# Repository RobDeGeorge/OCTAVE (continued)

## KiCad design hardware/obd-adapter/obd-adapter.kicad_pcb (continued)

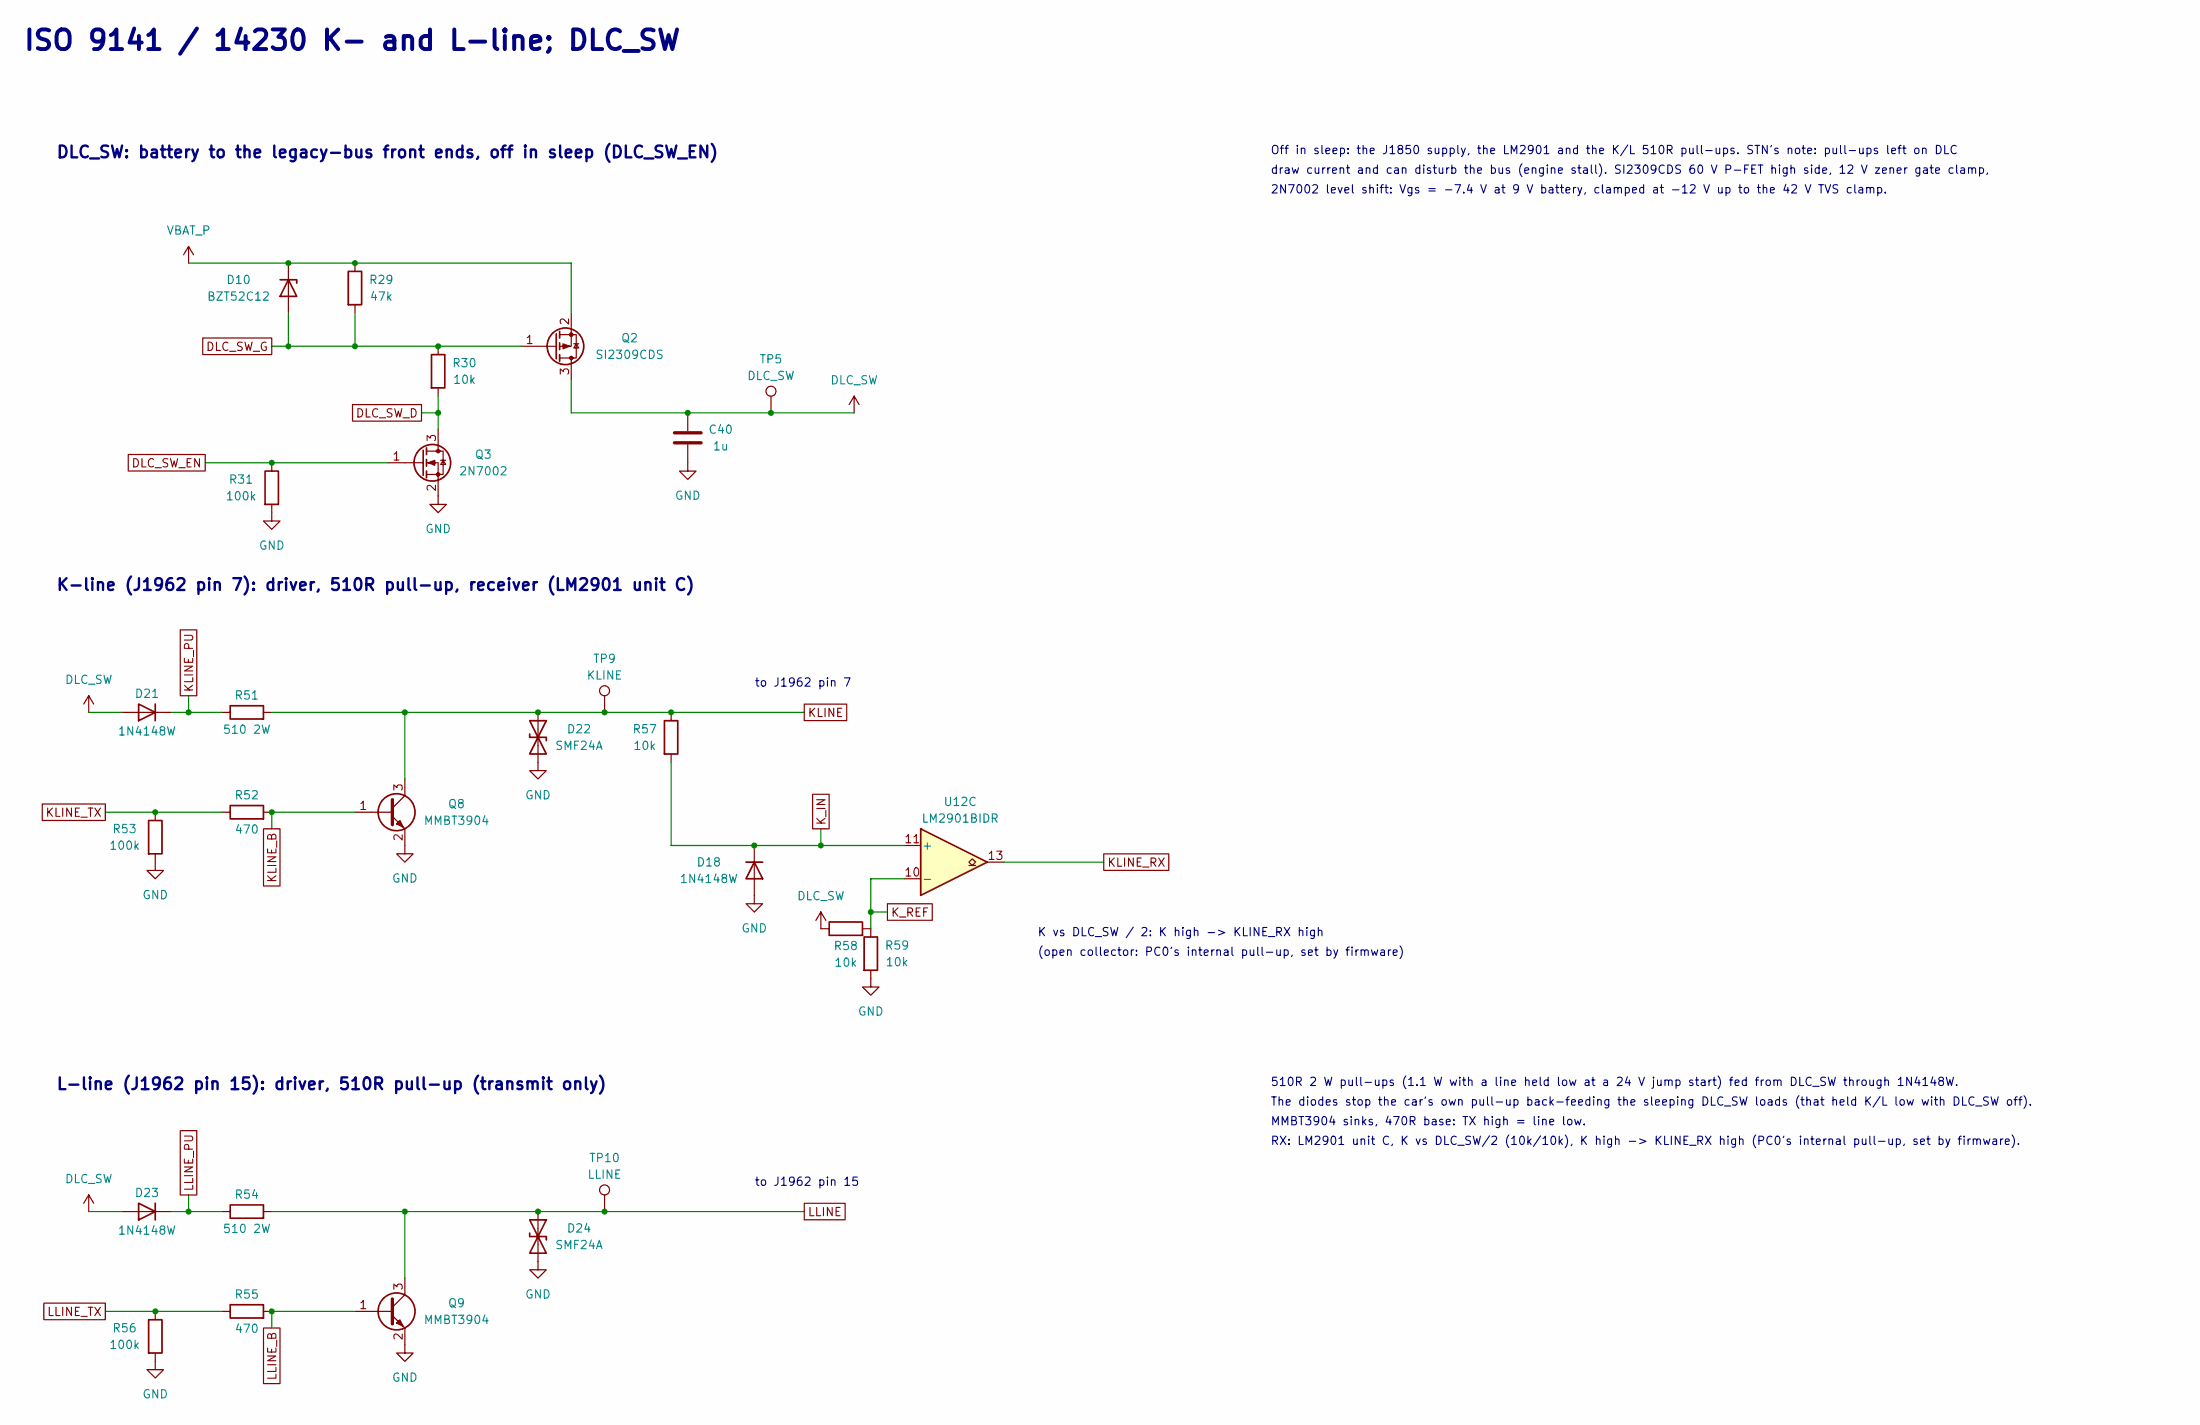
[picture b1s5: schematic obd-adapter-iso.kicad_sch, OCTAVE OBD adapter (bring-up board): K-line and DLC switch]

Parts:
C40: 1u; C_0603_1608Metric; LCSC C15849
D10: BZT52C12; D_SOD-123; LCSC C19077410
D18, D21, D23: 1N4148W; D_SOD-123; LCSC C81598
D22, D24: SMF24A; D_SOD-123F; LCSC C19077514
Q2: SI2309CDS; SOT-23; LCSC C10493
Q3: 2N7002; SOT-23; LCSC C8545
Q8, Q9: MMBT3904; SOT-23; LCSC C20526
R29: 47k; R_0603_1608Metric; LCSC C25819
R30: 10k; R_1206_3216Metric; LCSC C17902
R31, R53, R56: 100k; R_0603_1608Metric; LCSC C25803
R51, R54: 510 2W; R_2512_6332Metric; LCSC C5843118
R52, R55: 470; R_0603_1608Metric; LCSC C23179
R57, R58, R59: 10k; R_0603_1608Metric; LCSC C25804
TP5: DLC_SW; TestPoint_Pad_D1.5mm
TP9: KLINE; TestPoint_Pad_D1.5mm
TP10: LLINE; TestPoint_Pad_D1.5mm
U12: LM2901BIDR; SOIC-14_3.9x8.7mm_P1.27mm; LCSC C22427890

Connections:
DLC_SW: C40.1, D21.2 (A), D23.2 (A), Q2.3 (D), R58.1, TP5.1; also elsewhere on the board
DLC_SW_D: Q3.3 (D), R30.2
DLC_SW_EN: Q3.1 (G), R31.1; also elsewhere on the board
DLC_SW_G: D10.2 (A), Q2.1 (G), R29.2, R30.1
GND: C40.2, D18.2 (A), D22.2 (A2), D24.2 (A2), Q3.2 (S), Q8.2 (E), Q9.2 (E), R31.2, R53.2, R56.2, R59.2; also elsewhere on the board
KLINE: D22.1 (A1), Q8.3 (C), R51.2, R57.1, TP9.1; also elsewhere on the board
KLINE_B: Q8.1 (B), R52.2
KLINE_PU: D21.1 (K), R51.1
KLINE_RX: U12.13; also elsewhere on the board
KLINE_TX: R52.1, R53.1; also elsewhere on the board
K_IN: D18.1 (K), R57.2, U12.11 (+)
K_REF: R58.2, R59.1, U12.10 (-)
LLINE: D24.1 (A1), Q9.3 (C), R54.2, TP10.1; also elsewhere on the board
LLINE_B: Q9.1 (B), R55.2
LLINE_PU: D23.1 (K), R54.1
LLINE_TX: R55.1, R56.1; also elsewhere on the board
VBAT_P: D10.1 (K), Q2.2 (S), R29.1; also elsewhere on the board

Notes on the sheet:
ISO 9141 / 14230 K- and L-line; DLC_SW
DLC_SW: battery to the legacy-bus front ends, off in sleep (DLC_SW_EN)
K-line (J1962 pin 7): driver, 510R pull-up, receiver (LM2901 unit C)
to J1962 pin 7
K vs DLC_SW / 2: K high -> KLINE_RX high
(open collector: PC0's internal pull-up, set by firmware)
L-line (J1962 pin 15): driver, 510R pull-up (transmit only)
to J1962 pin 15
510R 2 W pull-ups (1.1 W with a line held low at a 24 V jump start) fed from DLC_SW through 1N4148W.
The diodes stop the car's own pull-up back-feeding the sleeping DLC_SW loads (that held K/L low with DLC_SW off).
MMBT3904 sinks, 470R base: TX high = line low.
RX: LM2901 unit C, K vs DLC_SW/2 (10k/10k), K high -> KLINE_RX high (PC0's internal pull-up, set by firmware).
Off in sleep: the J1850 supply, the LM2901 and the K/L 510R pull-ups. STN's note: pull-ups left on DLC
draw current and can disturb the bus (engine stall). SI2309CDS 60 V P-FET high side, 12 V zener gate clamp,
2N7002 level shift: Vgs = -7.4 V at 9 V battery, clamped at -12 V up to the 42 V TVS clamp.

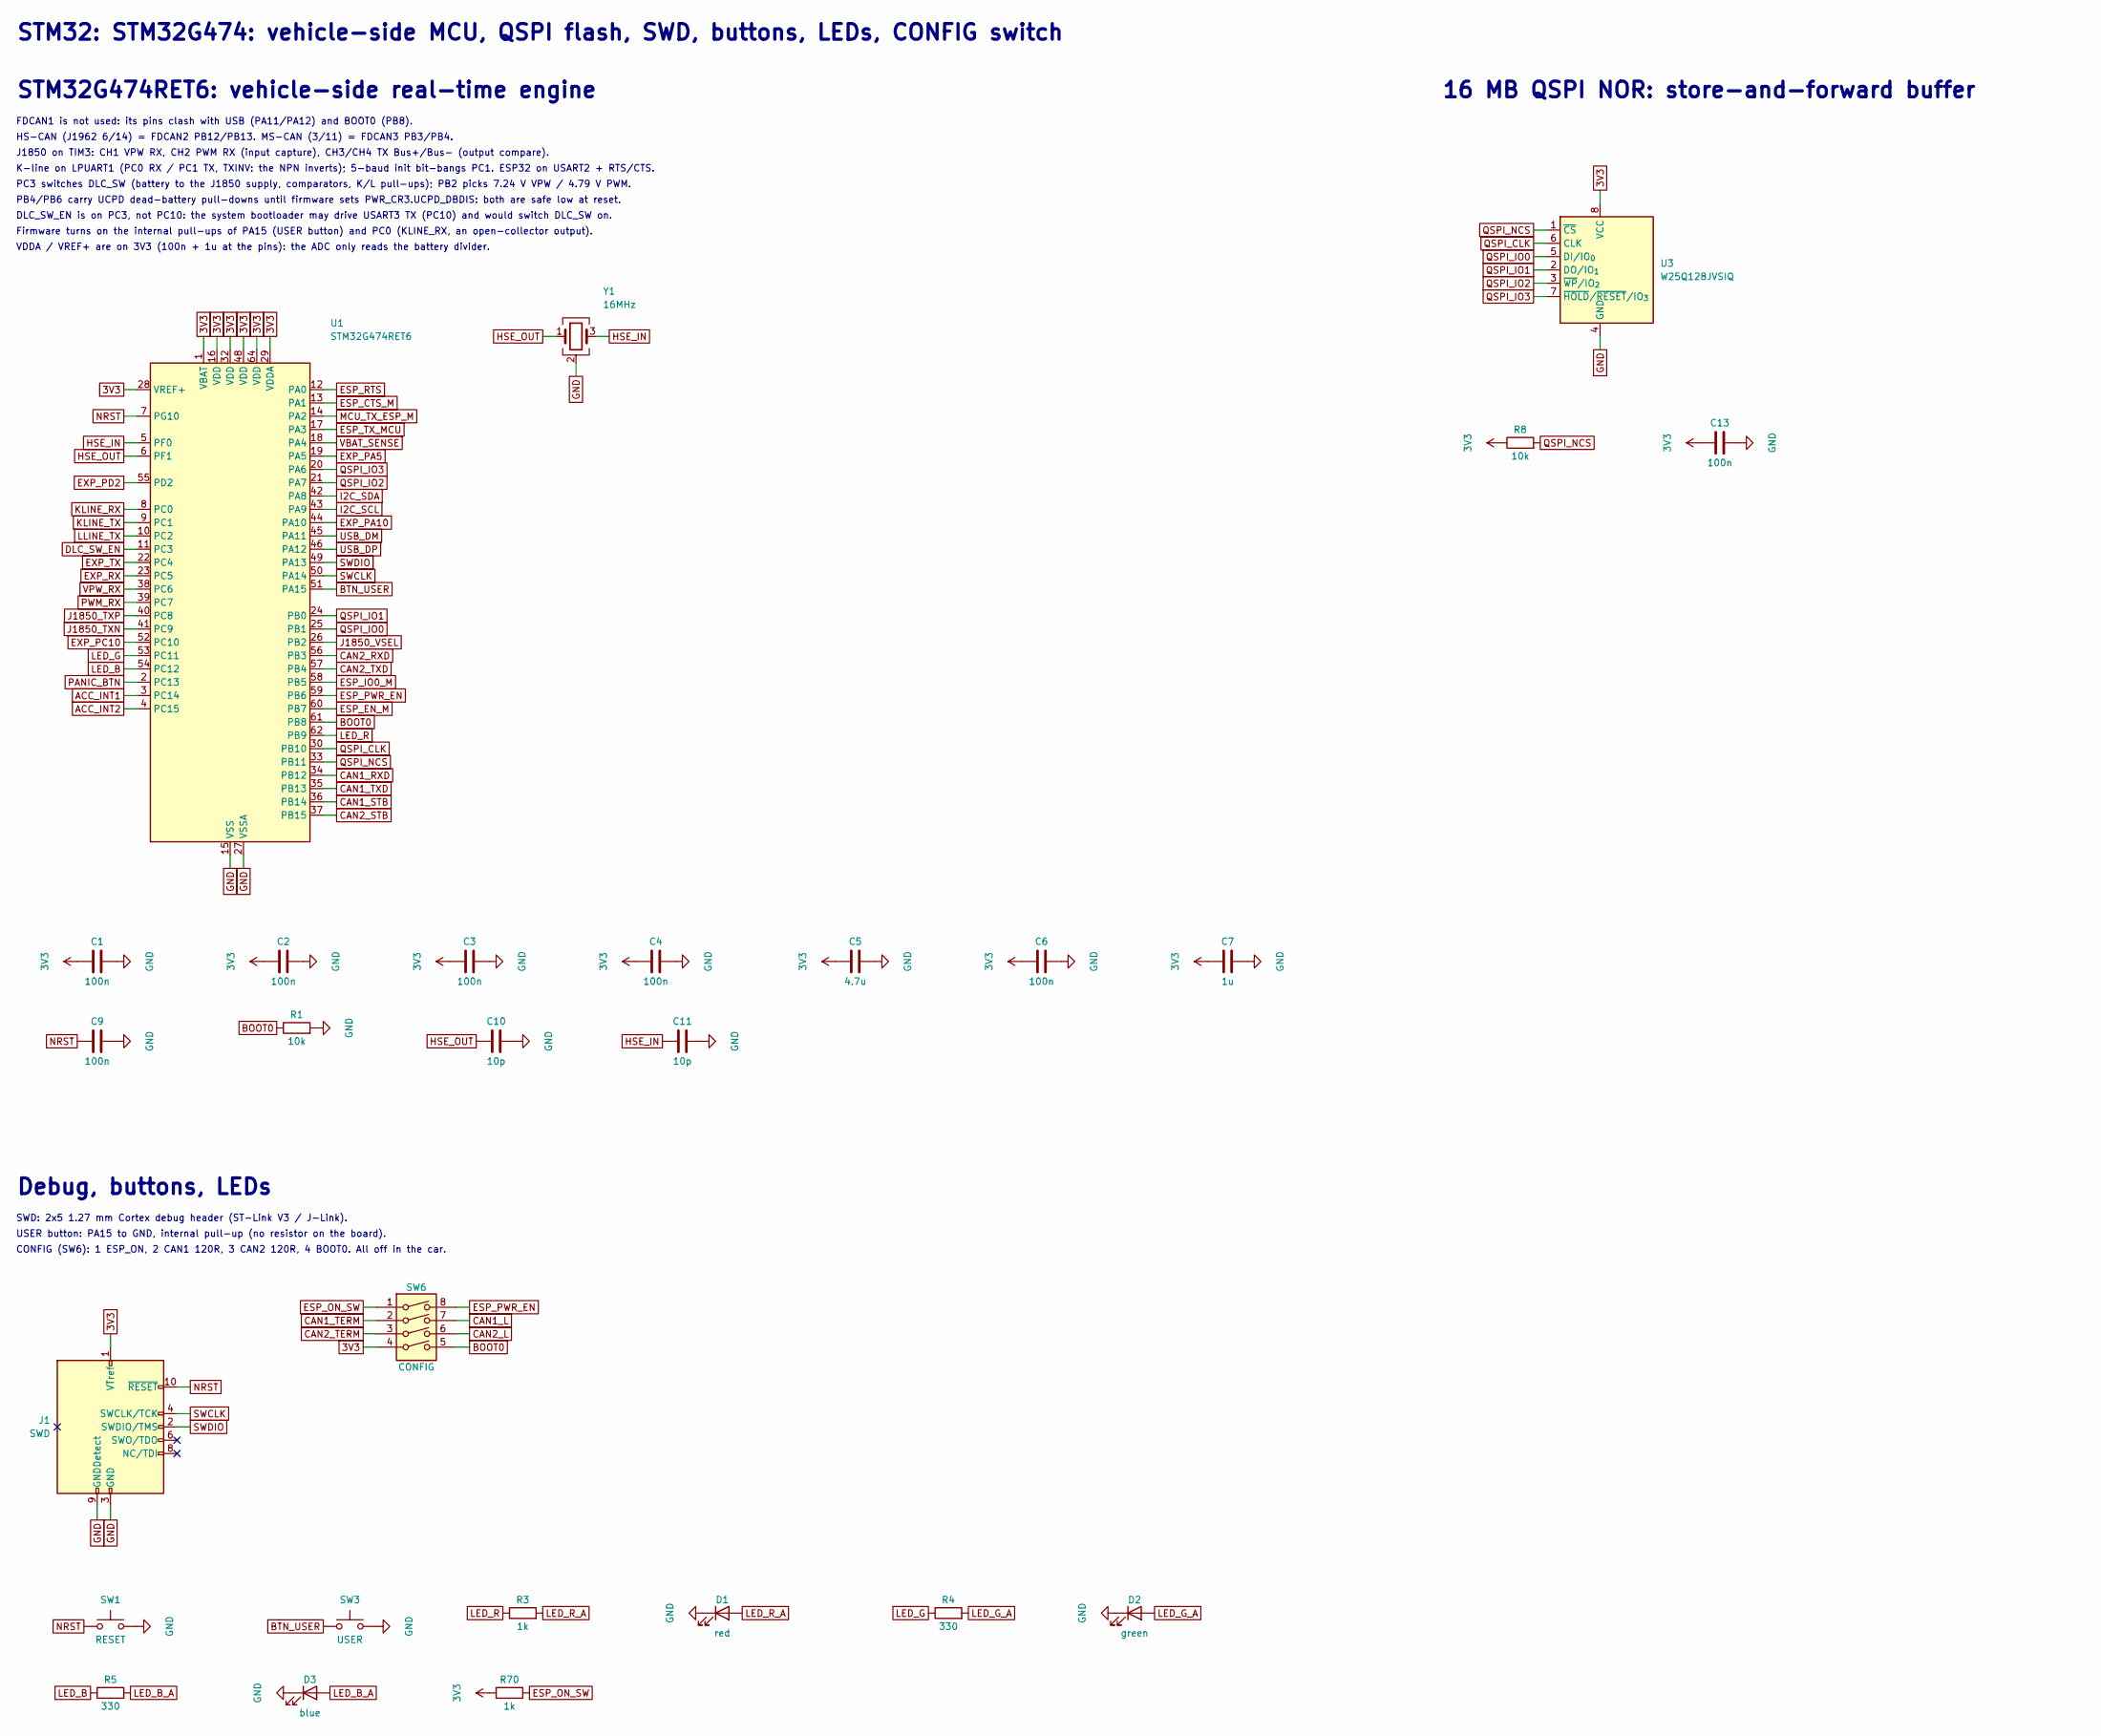
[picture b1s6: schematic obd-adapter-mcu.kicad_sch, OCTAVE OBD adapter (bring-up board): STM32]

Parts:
C1, C2, C3, C4, C6, C9, C13: 100n; C_0603_1608Metric; LCSC C14663
C5: 4.7u; C_0603_1608Metric; LCSC C19666
C7: 1u; C_0603_1608Metric; LCSC C15849
C10, C11: 10p; C_0603_1608Metric; LCSC C1634
D1: red; LED_0603_1608Metric; LCSC C2286
D2: green; LED_0603_1608Metric; LCSC C12624
D3: blue; LED_0603_1608Metric; LCSC C2288
J1: SWD; PinHeader_2x05_P1.27mm_Vertical_SMD; LCSC C41376037
R1, R8: 10k; R_0603_1608Metric; LCSC C25804
R3, R70: 1k; R_0603_1608Metric; LCSC C21190
R4, R5: 330; R_0603_1608Metric; LCSC C23138
SW1: RESET; SW_Push_1P1T_XKB_TS-1187A; LCSC C318884
SW3: USER; SW_Push_1P1T_XKB_TS-1187A; LCSC C318884
SW6: CONFIG; SW_DIP_SPSTx04_Slide_KingTek_DSHP04TS_W7.62mm_P1.27mm; LCSC C40736
U1: STM32G474RET6; LQFP-64_10x10mm_P0.5mm; LCSC C521608
U3: W25Q128JVSIQ; SOIC-8_5.3x5.3mm_P1.27mm; LCSC C97521
Y1: 16MHz; Crystal_SMD_3225-4Pin_3.2x2.5mm; LCSC C13738

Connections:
3V3: C1.1, C2.1, C3.1, C4.1, C5.1, C6.1, C7.1, C13.1, J1.1 (VTref), R8.1, R70.1, SW6.4, U1.1 (VBAT), U1.16 (VDD), U1.28 (VREF+), U1.29 (VDDA), U1.32 (VDD), U1.48 (VDD), U1.64 (VDD), U3.8 (VCC); also elsewhere on the board
ACC_INT1: U1.3 (PC14); also elsewhere on the board
ACC_INT2: U1.4 (PC15); also elsewhere on the board
BOOT0: R1.1, SW6.5, U1.61 (PB8)
BTN_USER: SW3.1, U1.51 (PA15)
CAN1_L: SW6.7; also elsewhere on the board
CAN1_RXD: U1.34 (PB12); also elsewhere on the board
CAN1_STB: U1.36 (PB14); also elsewhere on the board
CAN1_TERM: SW6.2; also elsewhere on the board
CAN1_TXD: U1.35 (PB13); also elsewhere on the board
CAN2_L: SW6.6; also elsewhere on the board
CAN2_RXD: U1.56 (PB3); also elsewhere on the board
CAN2_STB: U1.37 (PB15); also elsewhere on the board
CAN2_TERM: SW6.3; also elsewhere on the board
CAN2_TXD: U1.57 (PB4); also elsewhere on the board
DLC_SW_EN: U1.11 (PC3); also elsewhere on the board
ESP_CTS_M: U1.13 (PA1); also elsewhere on the board
ESP_EN_M: U1.60 (PB7); also elsewhere on the board
ESP_IO0_M: U1.58 (PB5); also elsewhere on the board
ESP_ON_SW: R70.2, SW6.1
ESP_PWR_EN: SW6.8, U1.59 (PB6); also elsewhere on the board
ESP_RTS: U1.12 (PA0); also elsewhere on the board
ESP_TX_MCU: U1.17 (PA3); also elsewhere on the board
EXP_PA5: U1.19 (PA5); also elsewhere on the board
EXP_PA10: U1.44 (PA10); also elsewhere on the board
EXP_PC10: U1.52 (PC10); also elsewhere on the board
EXP_PD2: U1.55 (PD2); also elsewhere on the board
EXP_RX: U1.23 (PC5); also elsewhere on the board
EXP_TX: U1.22 (PC4); also elsewhere on the board
GND: C1.2, C2.2, C3.2, C4.2, C5.2, C6.2, C7.2, C9.2, C10.2, C11.2, C13.2, D1.1 (K), D2.1 (K), D3.1 (K), J1.3 (GND), J1.5 (GND), J1.9 (GNDDetect), R1.2, SW1.2, SW3.2, U1.15 (VSS), U1.27 (VSSA), U1.31 (VSS), U1.47 (VSS), U1.63 (VSS), U3.4 (GND), Y1.2 (G), Y1.4 (G); also elsewhere on the board
HSE_IN: C11.1, U1.5 (PF0), Y1.3
HSE_OUT: C10.1, U1.6 (PF1), Y1.1
I2C_SCL: U1.43 (PA9); also elsewhere on the board
I2C_SDA: U1.42 (PA8); also elsewhere on the board
J1850_TXN: U1.41 (PC9); also elsewhere on the board
J1850_TXP: U1.40 (PC8); also elsewhere on the board
J1850_VSEL: U1.26 (PB2); also elsewhere on the board
KLINE_RX: U1.8 (PC0); also elsewhere on the board
KLINE_TX: U1.9 (PC1); also elsewhere on the board
LED_B: R5.1, U1.54 (PC12)
LED_B_A: D3.2 (A), R5.2
LED_G: R4.1, U1.53 (PC11)
LED_G_A: D2.2 (A), R4.2
LED_R: R3.1, U1.62 (PB9)
LED_R_A: D1.2 (A), R3.2
LLINE_TX: U1.10 (PC2); also elsewhere on the board
MCU_TX_ESP_M: U1.14 (PA2); also elsewhere on the board
NRST: C9.1, J1.10 (~RESET), SW1.1, U1.7 (PG10)
PANIC_BTN: U1.2 (PC13); also elsewhere on the board
PWM_RX: U1.39 (PC7); also elsewhere on the board
QSPI_CLK: U1.30 (PB10), U3.6 (CLK)
QSPI_IO0: U1.25 (PB1), U3.5 (DI/IO_{0})
QSPI_IO1: U1.24 (PB0), U3.2 (DO/IO_{1})
QSPI_IO2: U1.21 (PA7), U3.3 (~WP/IO_{2})
QSPI_IO3: U1.20 (PA6), U3.7 (~HOLD/~RESET/IO_{3})
QSPI_NCS: R8.2, U1.33 (PB11), U3.1 (~CS)
SWCLK: J1.4 (SWCLK/TCK), U1.50 (PA14)
SWDIO: J1.2 (SWDIO/TMS), U1.49 (PA13)
USB_DM: U1.45 (PA11); also elsewhere on the board
USB_DP: U1.46 (PA12); also elsewhere on the board
VBAT_SENSE: U1.18 (PA4); also elsewhere on the board
VPW_RX: U1.38 (PC6); also elsewhere on the board

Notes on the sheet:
STM32: STM32G474: vehicle-side MCU, QSPI flash, SWD, buttons, LEDs, CONFIG switch
STM32G474RET6: vehicle-side real-time engine
FDCAN1 is not used: its pins clash with USB (PA11/PA12) and BOOT0 (PB8).
HS-CAN (J1962 6/14) = FDCAN2 PB12/PB13. MS-CAN (3/11) = FDCAN3 PB3/PB4.
J1850 on TIM3: CH1 VPW RX, CH2 PWM RX (input capture), CH3/CH4 TX Bus+/Bus- (output compare).
K-line on LPUART1 (PC0 RX / PC1 TX, TXINV: the NPN inverts); 5-baud init bit-bangs PC1. ESP32 on USART2 + RTS/CTS.
PC3 switches DLC_SW (battery to the J1850 supply, comparators, K/L pull-ups); PB2 picks 7.24 V VPW / 4.79 V PWM.
PB4/PB6 carry UCPD dead-battery pull-downs until firmware sets PWR_CR3.UCPD_DBDIS: both are safe low at reset.
DLC_SW_EN is on PC3, not PC10: the system bootloader may drive USART3 TX (PC10) and would switch DLC_SW on.
Firmware turns on the internal pull-ups of PA15 (USER button) and PC0 (KLINE_RX, an open-collector output).
VDDA / VREF+ are on 3V3 (100n + 1u at the pins): the ADC only reads the battery divider.
16 MB QSPI NOR: store-and-forward buffer
Debug, buttons, LEDs
SWD: 2x5 1.27 mm Cortex debug header (ST-Link V3 / J-Link).
USER button: PA15 to GND, internal pull-up (no resistor on the board).
CONFIG (SW6): 1 ESP_ON, 2 CAN1 120R, 3 CAN2 120R, 4 BOOT0. All off in the car.

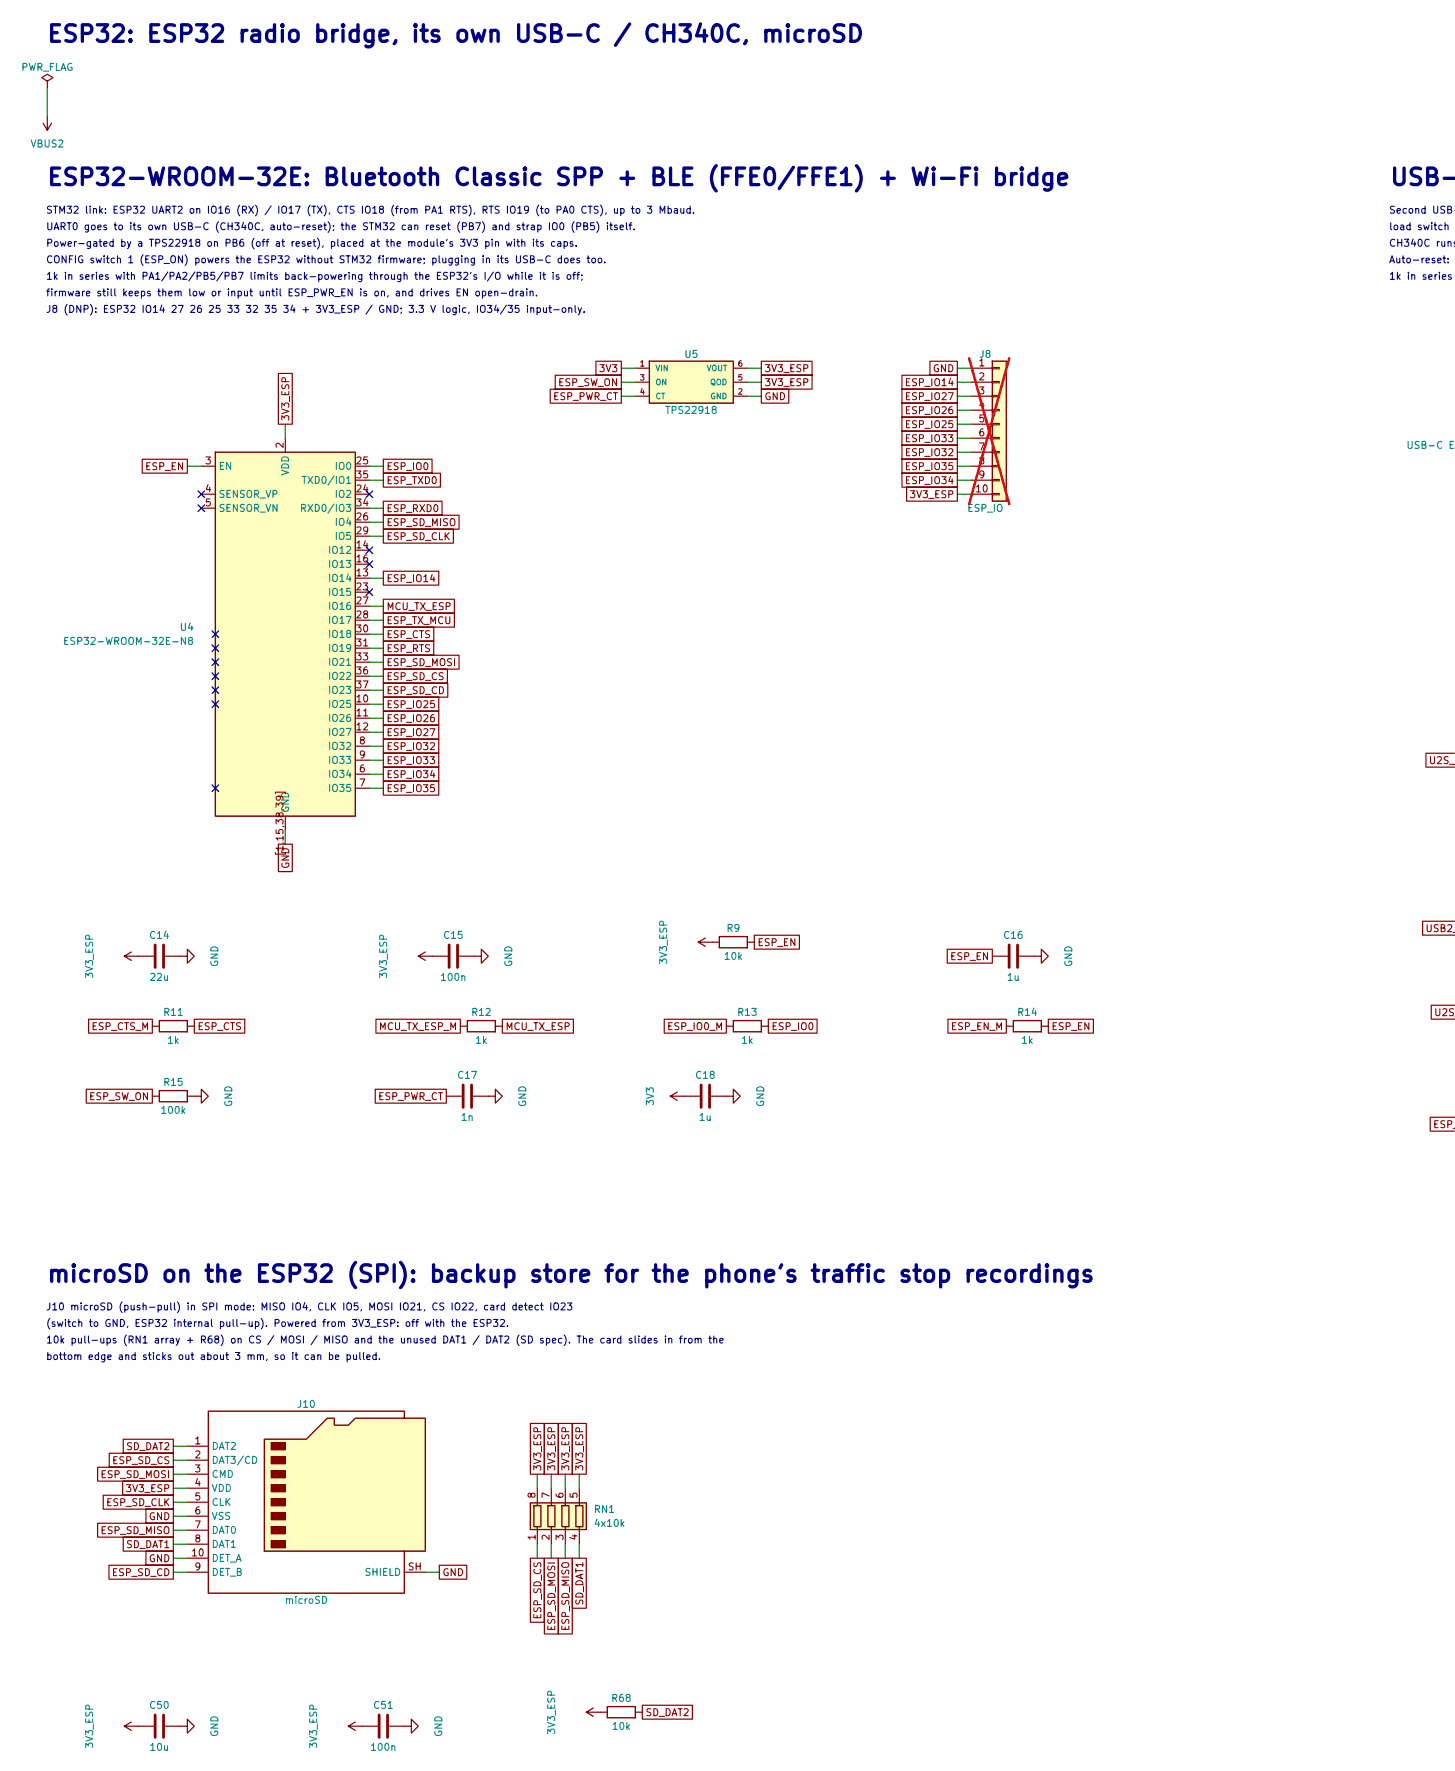
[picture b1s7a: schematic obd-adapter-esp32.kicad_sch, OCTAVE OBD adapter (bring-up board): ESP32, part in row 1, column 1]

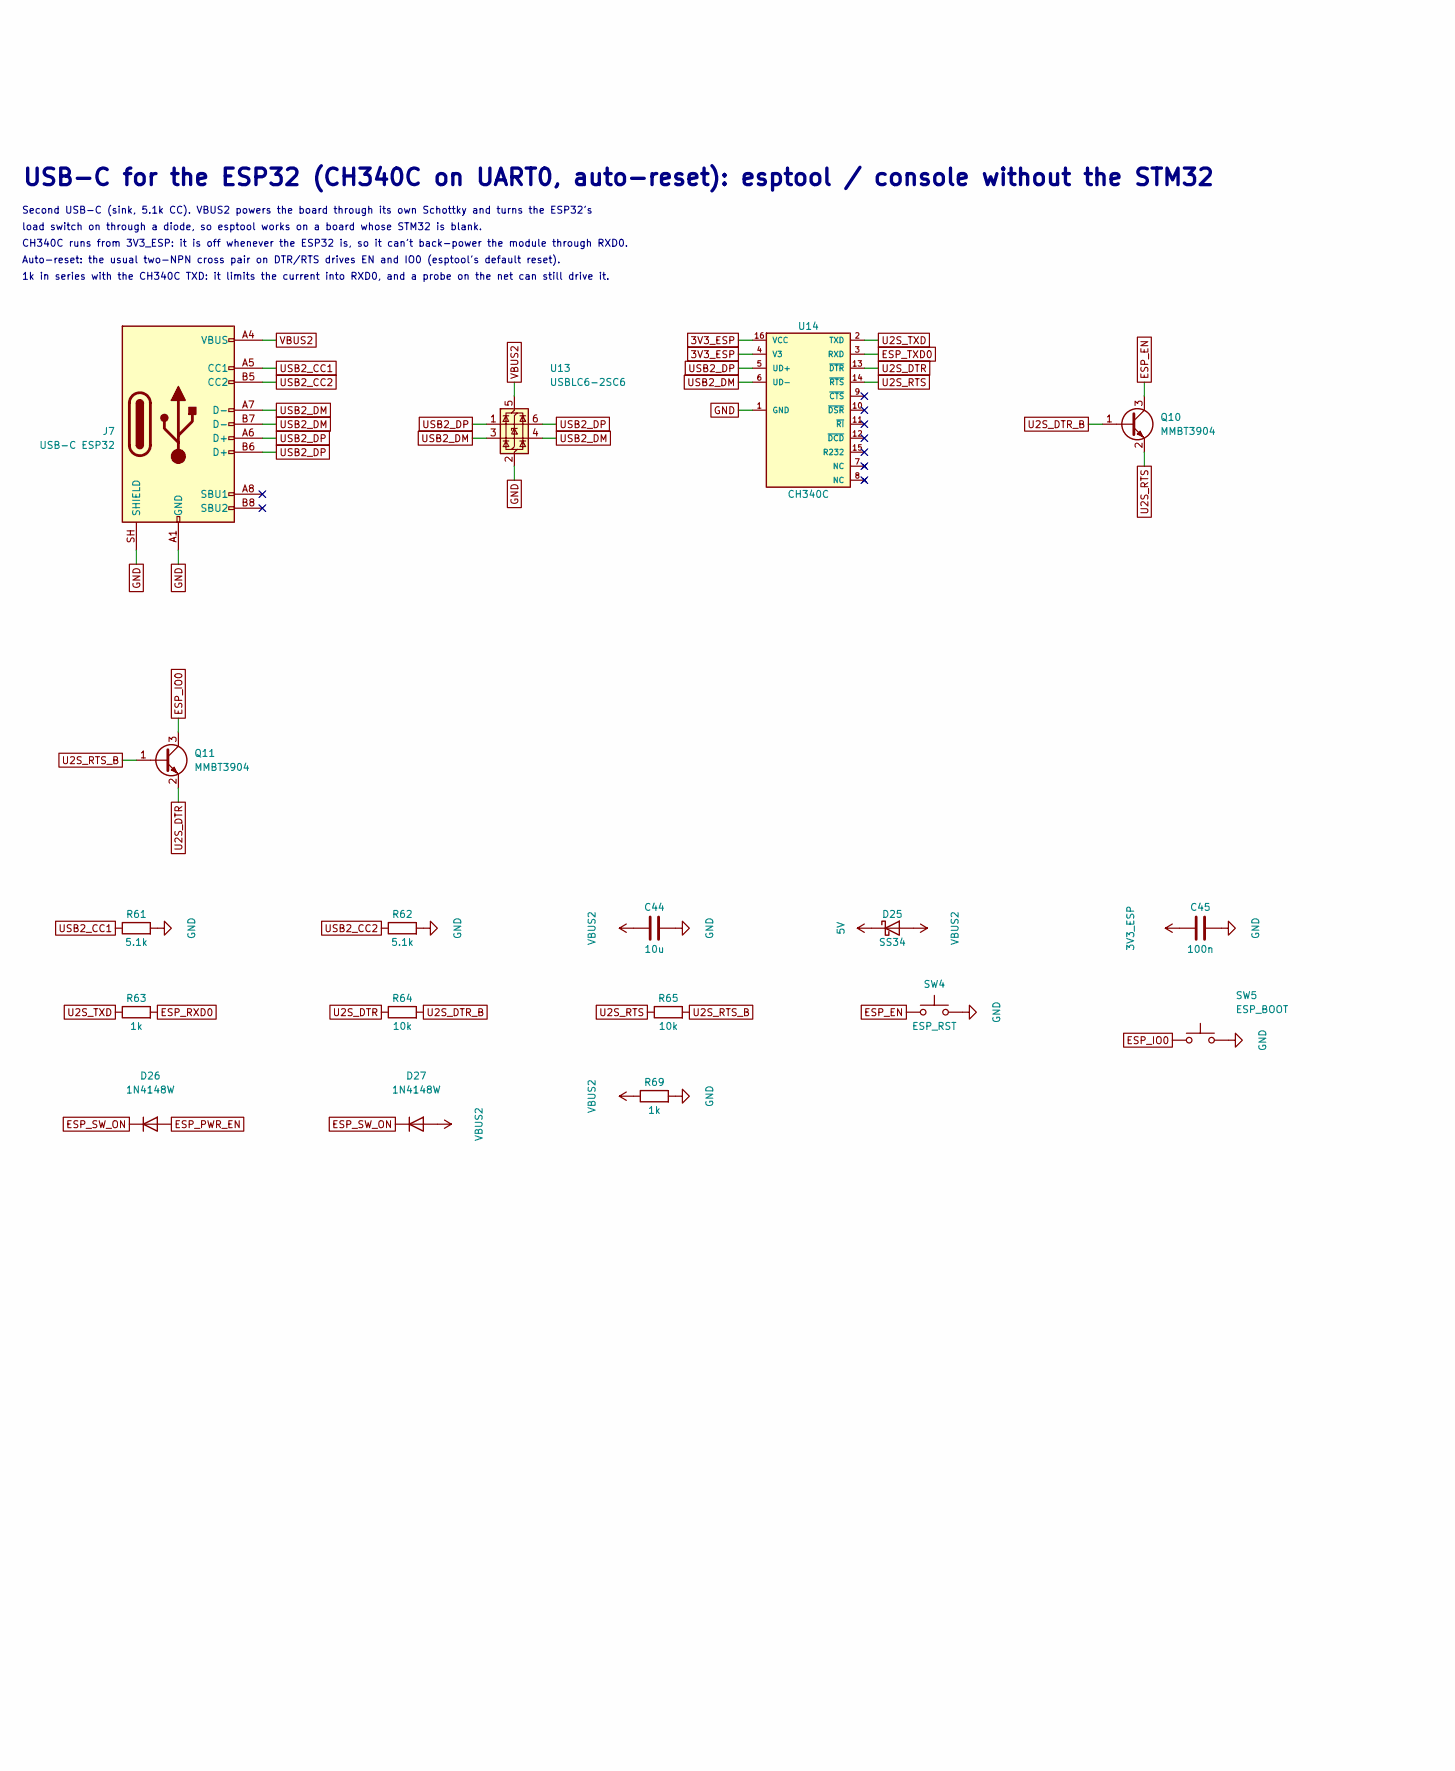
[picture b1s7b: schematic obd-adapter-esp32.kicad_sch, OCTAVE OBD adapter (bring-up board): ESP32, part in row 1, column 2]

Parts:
C14: 22u; C_1206_3216Metric; LCSC C12891
C15, C45, C51: 100n; C_0603_1608Metric; LCSC C14663
C16, C18: 1u; C_0603_1608Metric; LCSC C15849
C17: 1n; C_0603_1608Metric; LCSC C1588
C44, C50: 10u; C_0603_1608Metric; LCSC C96446
D25: SS34; D_SMA; LCSC C8678
D26, D27: 1N4148W; D_SOD-123; LCSC C81598
J7: USB-C ESP32; USB_C_Receptacle_HRO_TYPE-C-31-M-12; LCSC C165948
J8: ESP_IO; PinHeader_1x10_P2.54mm_Vertical; not fitted
J10: microSD; microSD_HC_Molex_104031-0811; LCSC C585350
Q10, Q11: MMBT3904; SOT-23; LCSC C20526
R9, R64, R65, R68: 10k; R_0603_1608Metric; LCSC C25804
R11, R12, R13, R14, R63, R69: 1k; R_0603_1608Metric; LCSC C21190
R15: 100k; R_0603_1608Metric; LCSC C25803
R61, R62: 5.1k; R_0603_1608Metric; LCSC C23186
RN1: 4x10k; R_Array_Convex_4x0603; LCSC C29718
SW4: ESP_RST; SW_Push_1P1T_XKB_TS-1187A; LCSC C318884
SW5: ESP_BOOT; SW_Push_1P1T_XKB_TS-1187A; LCSC C318884
U4: ESP32-WROOM-32E-N8; ESP32-WROOM-32E; LCSC C701342
U5: TPS22918; SOT-23-6; LCSC C131941
U13: USBLC6-2SC6; SOT-23-6; LCSC C2687116
U14: CH340C; SOIC-16_3.9x9.9mm_P1.27mm; LCSC C84681

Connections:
3V3: C18.1, U5.1 (VIN); also elsewhere on the board
3V3_ESP: C14.1, C15.1, C45.1, C50.1, C51.1, J8.10, J10.4 (VDD), R9.1, R68.1, RN1.5 (R4.2), RN1.6 (R3.2), RN1.7 (R2.2), RN1.8 (R1.2), U4.2 (VDD), U5.5 (QOD), U5.6 (VOUT), U14.4 (V3), U14.16 (VCC)
5V: D25.1 (K); also elsewhere on the board
ESP_CTS: R11.2, U4.30 (IO18)
ESP_CTS_M: R11.1; also elsewhere on the board
ESP_EN: C16.1, Q10.3 (C), R9.2, R14.2, SW4.1, U4.3 (EN)
ESP_EN_M: R14.1; also elsewhere on the board
ESP_IO0: Q11.3 (C), R13.2, SW5.1, U4.25 (IO0)
ESP_IO0_M: R13.1; also elsewhere on the board
ESP_IO14: J8.2, U4.13 (IO14)
ESP_IO25: J8.5, U4.10 (IO25)
ESP_IO26: J8.4, U4.11 (IO26)
ESP_IO27: J8.3, U4.12 (IO27)
ESP_IO32: J8.7, U4.8 (IO32)
ESP_IO33: J8.6, U4.9 (IO33)
ESP_IO34: J8.9, U4.6 (IO34)
ESP_IO35: J8.8, U4.7 (IO35)
ESP_PWR_CT: C17.1, U5.4 (CT)
ESP_PWR_EN: D26.2 (A); also elsewhere on the board
ESP_RTS: U4.31 (IO19); also elsewhere on the board
ESP_RXD0: R63.2, U4.34 (RXD0/IO3)
ESP_SD_CD: J10.9 (DET_B), U4.37 (IO23)
ESP_SD_CLK: J10.5 (CLK), U4.29 (IO5)
ESP_SD_CS: J10.2 (DAT3/CD), RN1.1 (R1.1), U4.36 (IO22)
ESP_SD_MISO: J10.7 (DAT0), RN1.3 (R3.1), U4.26 (IO4)
ESP_SD_MOSI: J10.3 (CMD), RN1.2 (R2.1), U4.33 (IO21)
ESP_SW_ON: D26.1 (K), D27.1 (K), R15.1, U5.3 (ON)
ESP_TXD0: U4.35 (TXD0/IO1), U14.3 (RXD)
ESP_TX_MCU: U4.28 (IO17); also elsewhere on the board
GND: C14.2, C15.2, C16.2, C17.2, C18.2, C44.2, C45.2, C50.2, C51.2, J7.A1 (GND), J7.A12 (GND), J7.B1 (GND), J7.B12 (GND), J7.SH (SHIELD), J8.1, J10.6 (VSS), J10.10 (DET_A), J10.SH (SHIELD), R15.2, R61.2, R62.2, R69.2, SW4.2, SW5.2, U4.1, U4.15, U4.38, U4.39, U4.[1,15,38,39] (GND), U5.2 (GND), U13.2 (GND), U14.1 (GND); also elsewhere on the board
MCU_TX_ESP: R12.2, U4.27 (IO16)
MCU_TX_ESP_M: R12.1; also elsewhere on the board
SD_DAT1: J10.8 (DAT1), RN1.4 (R4.1)
SD_DAT2: J10.1 (DAT2), R68.2
U2S_DTR: Q11.2 (E), R64.1, U14.13 (~DTR)
U2S_DTR_B: Q10.1 (B), R64.2
U2S_RTS: Q10.2 (E), R65.1, U14.14 (~RTS)
U2S_RTS_B: Q11.1 (B), R65.2
U2S_TXD: R63.1, U14.2 (TXD)
USB2_CC1: J7.A5 (CC1), R61.1
USB2_CC2: J7.B5 (CC2), R62.1
USB2_DM: J7.A7 (D-), J7.B7 (D-), U13.3 (I/O2), U13.4 (I/O2), U14.6 (UD-)
USB2_DP: J7.A6 (D+), J7.B6 (D+), U13.1 (I/O1), U13.6 (I/O1), U14.5 (UD+)
VBUS2: C44.1, D25.2 (A), D27.2 (A), J7.A4 (VBUS), J7.A9 (VBUS), J7.B4 (VBUS), J7.B9 (VBUS), R69.1, U13.5 (VBUS)

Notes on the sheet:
ESP32: ESP32 radio bridge, its own USB-C / CH340C, microSD
ESP32-WROOM-32E: Bluetooth Classic SPP + BLE (FFE0/FFE1) + Wi-Fi bridge
STM32 link: ESP32 UART2 on IO16 (RX) / IO17 (TX), CTS IO18 (from PA1 RTS), RTS IO19 (to PA0 CTS), up to 3 Mbaud.
UART0 goes to its own USB-C (CH340C, auto-reset); the STM32 can reset (PB7) and strap IO0 (PB5) itself.
Power-gated by a TPS22918 on PB6 (off at reset), placed at the module's 3V3 pin with its caps.
CONFIG switch 1 (ESP_ON) powers the ESP32 without STM32 firmware; plugging in its USB-C does too.
1k in series with PA1/PA2/PB5/PB7 limits back-powering through the ESP32's I/O while it is off;
firmware still keeps them low or input until ESP_PWR_EN is on, and drives EN open-drain.
J8 (DNP): ESP32 IO14 27 26 25 33 32 35 34 + 3V3_ESP / GND; 3.3 V logic, IO34/35 input-only.
USB-C for the ESP32 (CH340C on UART0, auto-reset): esptool / console without the STM32
Second USB-C (sink, 5.1k CC). VBUS2 powers the board through its own Schottky and turns the ESP32's
load switch on through a diode, so esptool works on a board whose STM32 is blank.
CH340C runs from 3V3_ESP: it is off whenever the ESP32 is, so it can't back-power the module through RXD0.
Auto-reset: the usual two-NPN cross pair on DTR/RTS drives EN and IO0 (esptool's default reset).
1k in series with the CH340C TXD: it limits the current into RXD0, and a probe on the net can still drive it.
microSD on the ESP32 (SPI): backup store for the phone's traffic stop recordings
J10 microSD (push-pull) in SPI mode: MISO IO4, CLK IO5, MOSI IO21, CS IO22, card detect IO23
(switch to GND, ESP32 internal pull-up). Powered from 3V3_ESP: off with the ESP32.
10k pull-ups (RN1 array + R68) on CS / MOSI / MISO and the unused DAT1 / DAT2 (SD spec). The card slides in from the
bottom edge and sticks out about 3 mm, so it can be pulled.
